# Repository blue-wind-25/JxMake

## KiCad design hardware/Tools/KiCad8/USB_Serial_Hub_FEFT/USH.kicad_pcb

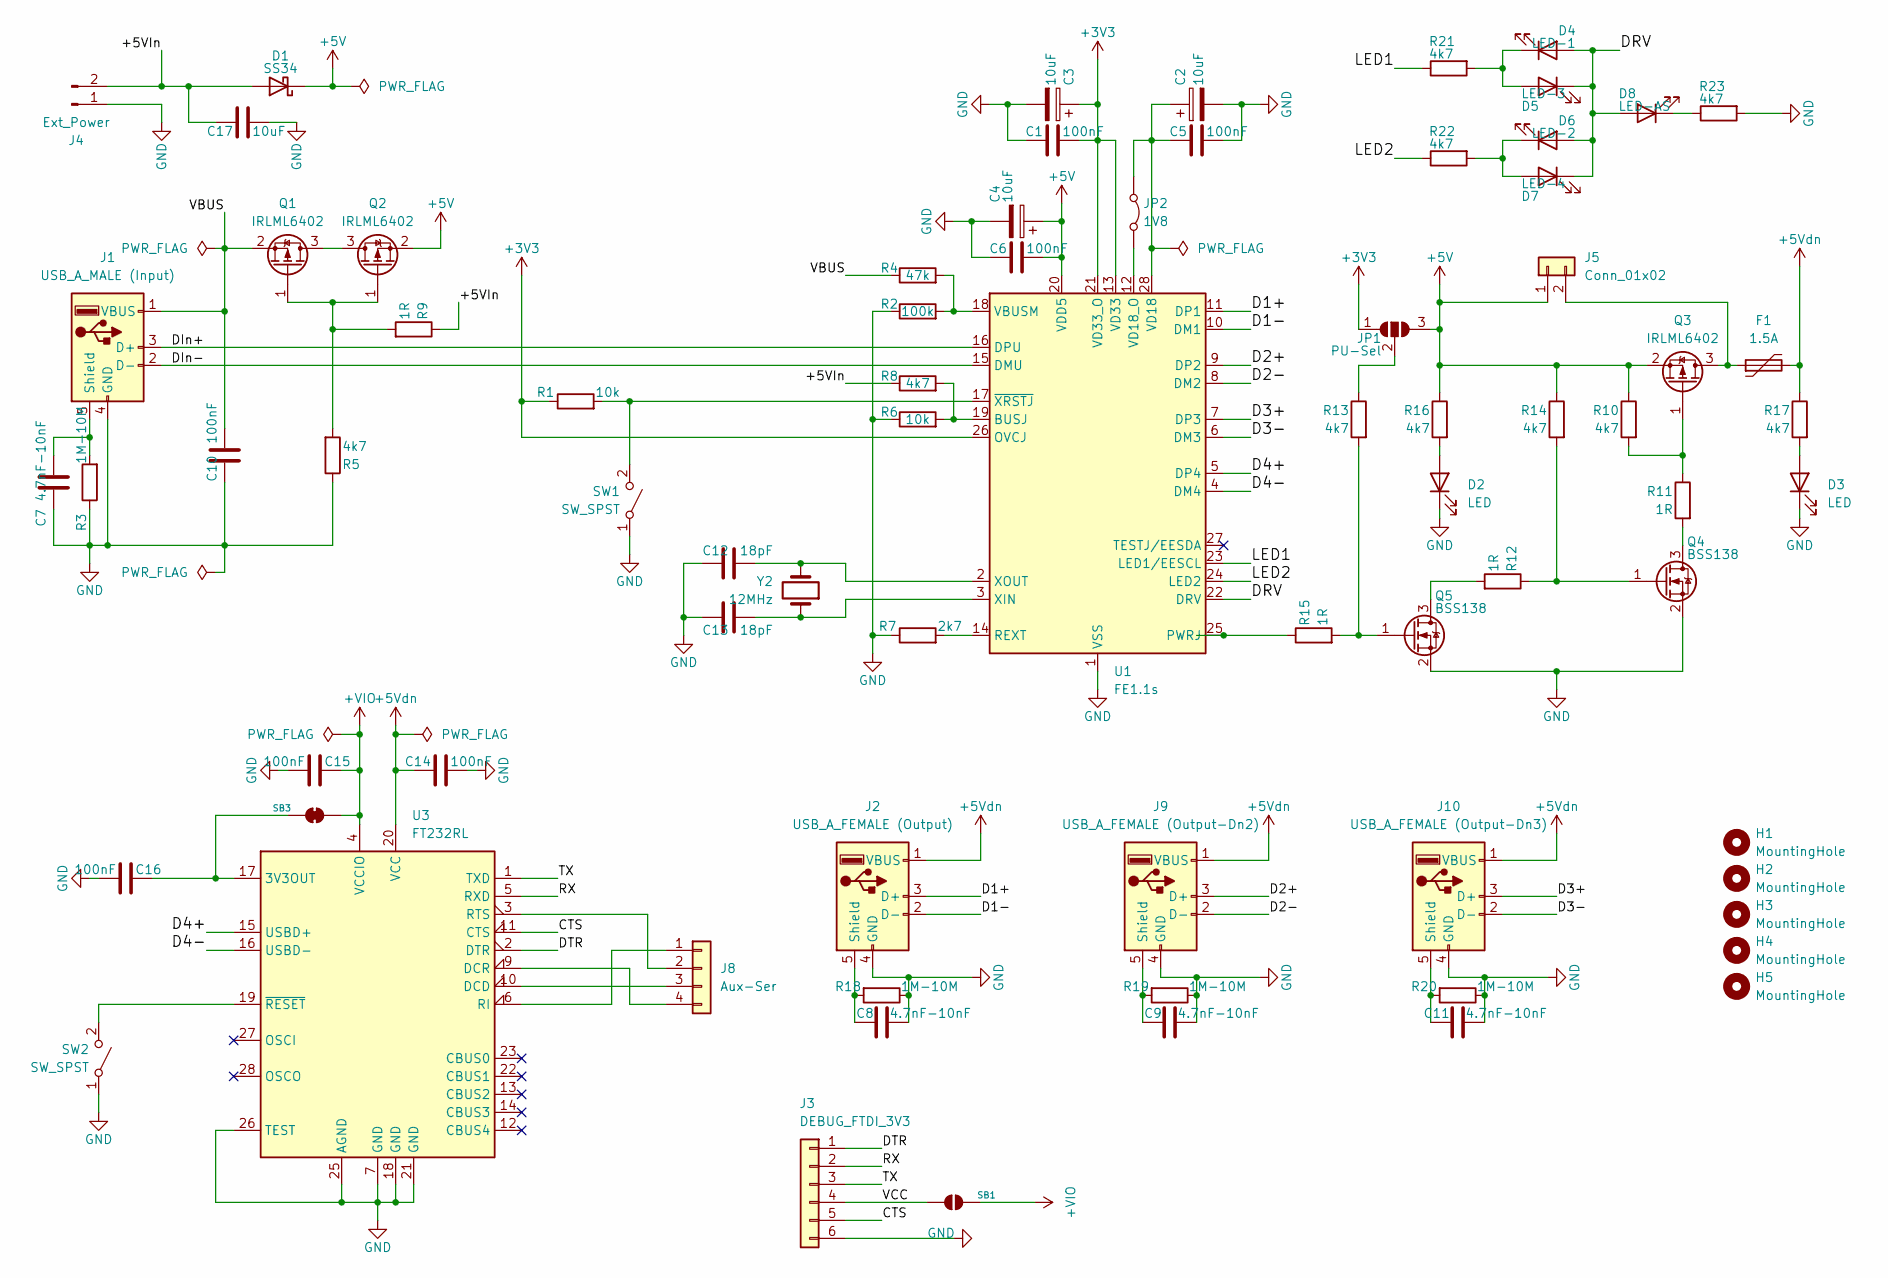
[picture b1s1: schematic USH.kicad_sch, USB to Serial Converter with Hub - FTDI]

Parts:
C1, C5, C6, C10, C14, C15, C16: 100nF; C_0805_2012Metric_Pad1.18x1.45mm_HandSolder
C2, C3, C4: 10uF; CP_EIA-3528-21_Kemet-B_Pad1.50x2.35mm_HandSolder
C7, C8, C9, C11: 4.7nF-10nF; C_0805_2012Metric_Pad1.18x1.45mm_HandSolder
C12, C13: 18pF; C_0805_2012Metric_Pad1.18x1.45mm_HandSolder
C17: 10uF; C_0805_2012Metric_Pad1.18x1.45mm_HandSolder
D1: SS34; D_SMB-SMC_Universal_Handsoldering
D2, D3: LED; LED_0805_2012Metric_Pad1.15x1.40mm_HandSolder
D4: LED-1; LED_0603_1608Metric_Pad1.05x0.95mm_HandSolder
D5: LED-3; LED_0603_1608Metric_Pad1.05x0.95mm_HandSolder
D6: LED-2; LED_0603_1608Metric_Pad1.05x0.95mm_HandSolder
D7: LED-4; LED_0603_1608Metric_Pad1.05x0.95mm_HandSolder
D8: LED-AS; LED_0603_1608Metric_Pad1.05x0.95mm_HandSolder
F1: 1.5A; R_1812_4532Metric_Pad1.30x3.40mm_HandSolder
H1, H2, H3, H4, H5: MountingHole; MountingHole_3.2mm_M3
J1: USB_A_MALE (Input); USB_A_CONNFLY_DS1095-WNR0
J2: USB_A_FEMALE (Output); USB_A_CONNFLY_DS1095-WNR0
J3: DEBUG_FTDI_3V3; PinHeader_1x06_P2.54mm_Horizontal
J4: Ext_Power; Molex_Nano-Fit_105313-xx02_1x02_P2.50mm_Horizontal
J5: Conn_01x02; PinHeader_1x02_P2.54mm_Vertical
J8: Aux-Ser; PinHeader_1x04_P1.00mm_Vertical
J9: USB_A_FEMALE (Output-Dn2); USB_A_CONNFLY_DS1095-WNR0
J10: USB_A_FEMALE (Output-Dn3); USB_A_CONNFLY_DS1095-WNR0
JP1: PU-Sel; SolderJumper-3_P1.3mm_Open_RoundedPad1.0x1.5mm
JP2: 1V8; SolderJumper-2_P1.3mm_Bridged_RoundedPad1.0x1.5mm
Q1, Q2, Q3: IRLML6402; SOT-23_Handsoldering
Q4, Q5: BSS138; SOT-23_Handsoldering
R1, R6: 10k; R_0805_2012Metric_Pad1.20x1.40mm_HandSolder
R2: 100k; R_0805_2012Metric_Pad1.20x1.40mm_HandSolder
R3, R18, R19, R20: 1M-10M; R_0805_2012Metric_Pad1.20x1.40mm_HandSolder
R4: 47k; R_0805_2012Metric_Pad1.20x1.40mm_HandSolder
R5, R8, R10, R13, R14, R16, R17: 4k7; R_0805_2012Metric_Pad1.20x1.40mm_HandSolder
R7: 2k7; R_0805_2012Metric_Pad1.20x1.40mm_HandSolder
R9, R11, R12, R15: 1R; R_0805_2012Metric_Pad1.20x1.40mm_HandSolder
R21, R22, R23: 4k7; R_0603_1608Metric_Pad0.98x0.95mm_HandSolder
SB1: Jumper_2_Small_Bridged; SolderJumper-2_P1.3mm_Open_RoundedPad1.0x1.5mm
SB3: Jumper_2_Small_Bridged; SolderJumper-2_P1.3mm_Bridged_RoundedPad1.0x1.5mm
SW1, SW2: SW_SPST; SW_SPST_FSMSM
U1: FE1.1s; SSOP-28_3.9x9.9mm_P0.635mm
U3: FT232RL; SSOP-28_5.3x10.2mm_P0.65mm
Y2: 12MHz; Crystal_SMD_HC49-SD

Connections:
+3V3: C1.1, C3.1, JP1.1 (A), R1.1, U1.13 (VD33), U1.21 (VD33_O), U1.26 (OVCJ)
+5V: C4.1, C6.1, D1.1 (K), J5.1, JP1.3 (B), Q2.2 (S), Q3.2 (S), R10.1, R14.1, R16.1, U1.20 (VDD5)
+5Vdn: C14.2, F1.2, J2.1 (VBUS), J9.1 (VBUS), J10.1 (VBUS), R17.1, U3.20 (VCC)
+VIO: C15.2, SB1.1 (A), SB3.2 (B), U3.4 (VCCIO)
/+5VIn: C17.2, D1.2 (A), J4.2, R8.1, R9.1
/CTS: J3.5, U3.11 (CTS)
/D1+: J2.3 (D+), U1.11 (DP1)
/D1-: J2.2 (D-), U1.10 (DM1)
/D2+: J9.3 (D+), U1.9 (DP2)
/D2-: J9.2 (D-), U1.8 (DM2)
/D3+: J10.3 (D+), U1.7 (DP3)
/D3-: J10.2 (D-), U1.6 (DM3)
/D4+: U1.5 (DP4), U3.15 (USBD+)
/D4-: U1.4 (DM4), U3.16 (USBD-)
/DIn+: J1.3 (D+), U1.16 (DPU)
/DIn-: J1.2 (D-), U1.15 (DMU)
/DRV: D4.2 (A), D5.1 (K), D6.2 (A), D7.1 (K), D8.2 (A), U1.22 (DRV)
/DTR: J3.1, U3.2 (DTR)
/LED1: R21.1, U1.23 (LED1/EESCL)
/LED2: R22.1, U1.24 (LED2)
/RX: J3.2, U3.5 (RXD)
/TX: J3.3, U3.1 (TXD)
/VBUS: C10.2, J1.1 (VBUS), Q1.2 (S), R4.1
/VCC: J3.4, SB1.2 (B)
GND: C1.2, C2.2, C3.2, C4.2, C5.1, C6.2, C7.1, C8.1, C9.1, C10.1, C11.1, C12.1, C13.1, C14.1, C15.1, C16.1, C17.1, D2.1 (K), D3.1 (K), J1.4 (GND), J2.4 (GND), J3.6, J4.1, J9.4 (GND), J10.4 (GND), Q4.2 (S), Q5.2 (S), R2.1, R3.1, R5.1, R6.1, R7.1, R18.1, R19.1, R20.1, R23.2, SW1.1 (A), SW2.1 (A), U1.1 (VSS), U3.7 (GND), U3.18 (GND), U3.21 (GND), U3.25 (AGND), U3.26 (TEST)
unnamed: D2.2 (A), R16.2
unnamed: D3.2 (A), R17.2
unnamed: D4.1 (K), D5.2 (A), R21.2
unnamed: D6.1 (K), D7.2 (A), R22.2
unnamed: D8.1 (K), R23.1
unnamed: C7.2, J1.5 (Shield), R3.2
unnamed: C8.2, J2.5 (Shield), R18.2
unnamed: F1.1, J5.2, Q3.3 (D)
unnamed: J8.1, U3.6 (RI)
unnamed: J8.2, U3.3 (RTS)
unnamed: J8.3, U3.10 (DCD)
unnamed: J8.4, U3.9 (DCR)
unnamed: C9.2, J9.5 (Shield), R19.2
unnamed: C11.2, J10.5 (Shield), R20.2
unnamed: JP1.2 (C), R13.1
unnamed: C2.1, C5.2, JP2.1 (A), U1.28 (VD18)
unnamed: JP2.2 (B), U1.12 (VD18_O)
unnamed: Q1.3 (D), Q2.3 (D)
unnamed: Q1.1 (G), Q2.1 (G), R5.2, R9.2
unnamed: Q3.1 (G), R10.2, R11.1
unnamed: Q4.3 (D), R11.2
unnamed: Q4.1 (G), R12.1, R14.2
unnamed: Q5.3 (D), R12.2
unnamed: Q5.1 (G), R13.2, R15.2
unnamed: C16.2, SB3.1 (A), U3.17 (3V3OUT)
unnamed: R1.2, SW1.2 (B), U1.17 (~XRSTJ)
unnamed: SW2.2 (B), U3.19 (~RESET)
unnamed: R6.2, R8.2, U1.19 (BUSJ)
unnamed: R15.1, U1.25 (PWRJ)
unnamed: R7.2, U1.14 (REXT)
unnamed: R2.2, R4.2, U1.18 (VBUSM)
unnamed: C13.2, U1.3 (XIN), Y2.1
unnamed: C12.2, U1.2 (XOUT), Y2.2

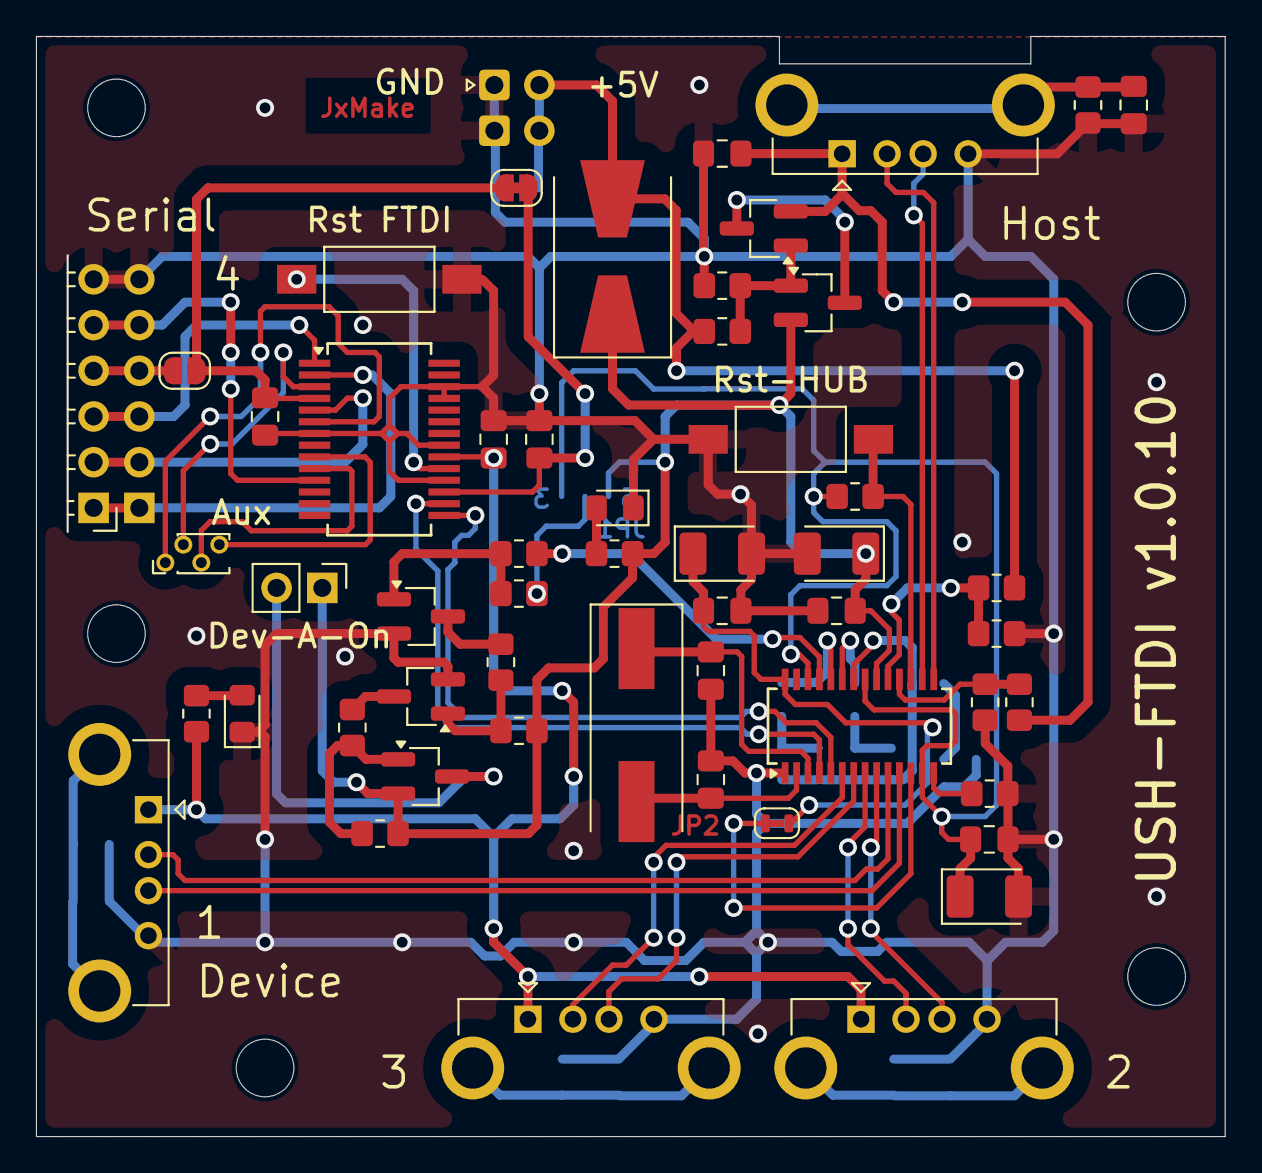
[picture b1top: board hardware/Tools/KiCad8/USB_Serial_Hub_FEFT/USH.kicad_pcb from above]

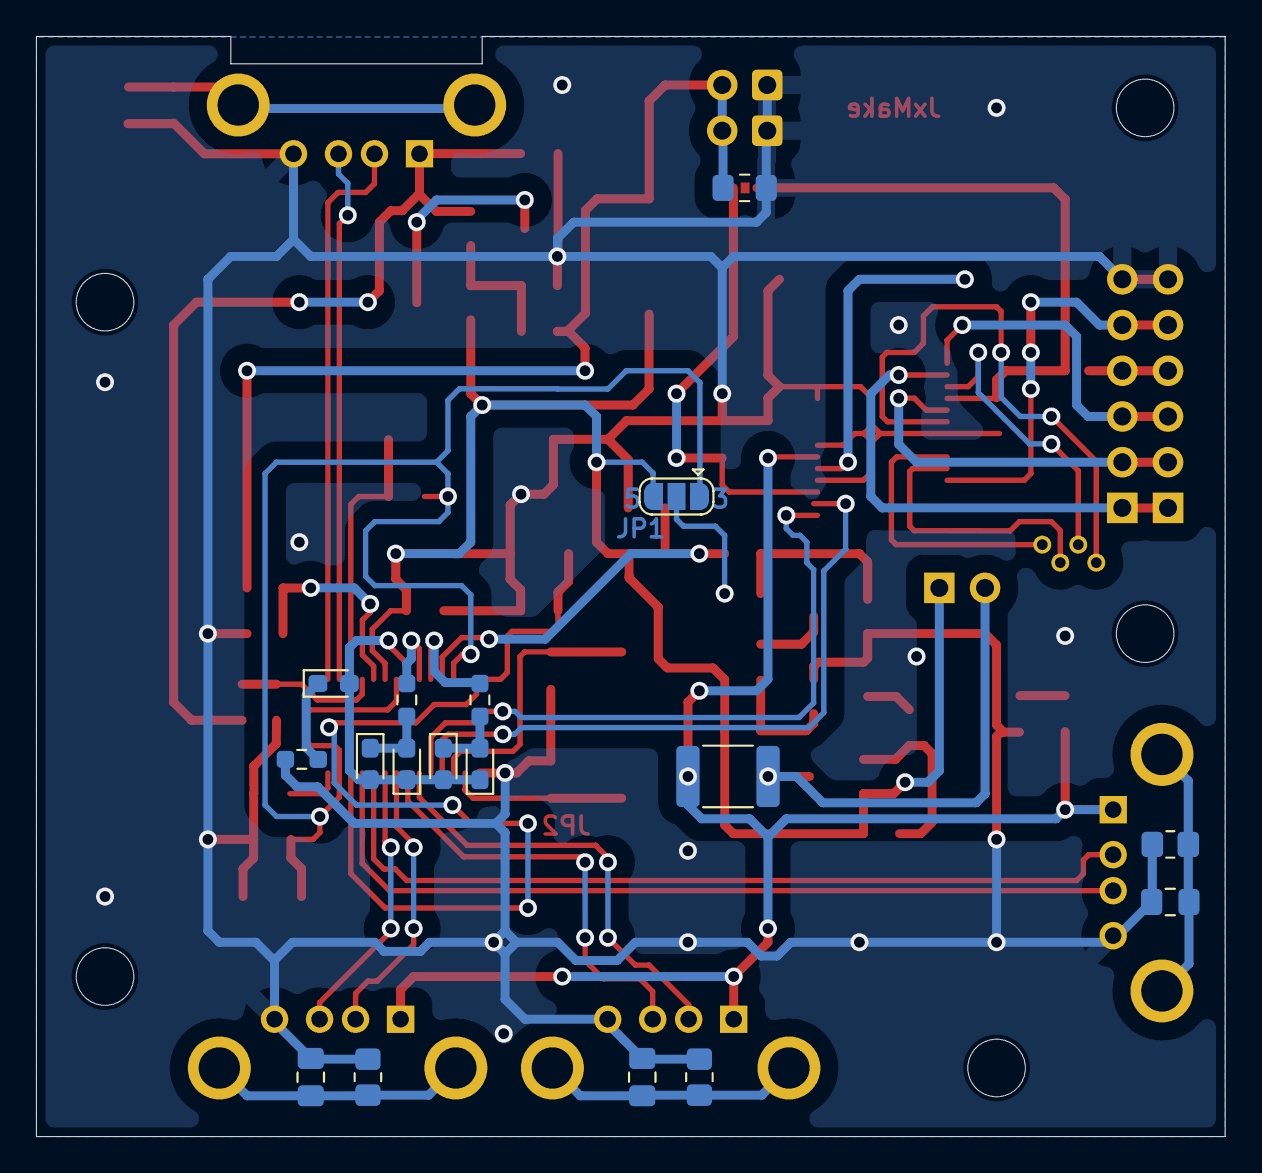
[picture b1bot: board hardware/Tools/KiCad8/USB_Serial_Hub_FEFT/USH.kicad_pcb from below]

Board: 2 copper layers, 66.0 x 61.1 mm, 76 parts (18 on the bottom side), 58 nets.

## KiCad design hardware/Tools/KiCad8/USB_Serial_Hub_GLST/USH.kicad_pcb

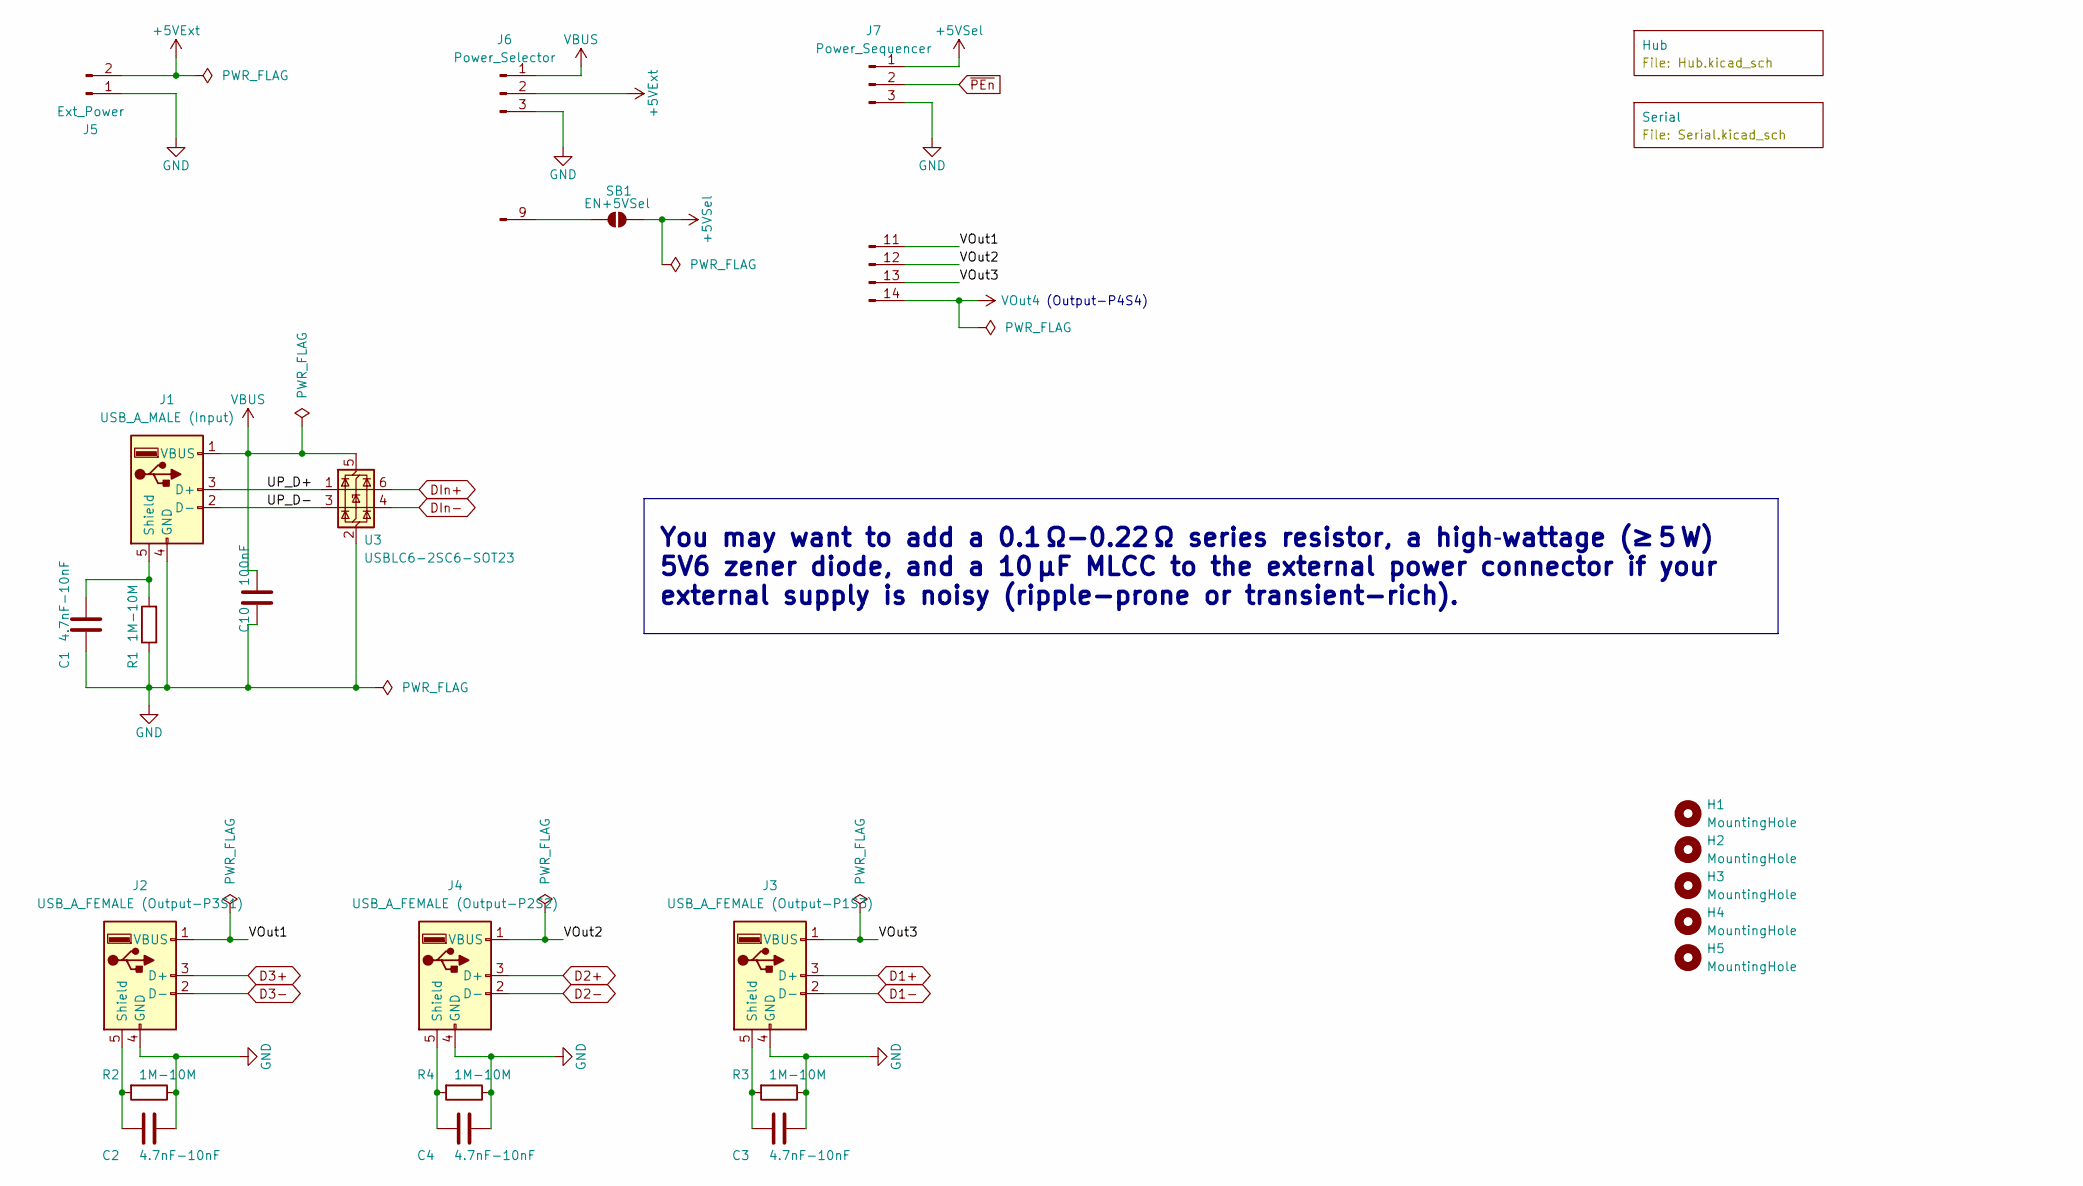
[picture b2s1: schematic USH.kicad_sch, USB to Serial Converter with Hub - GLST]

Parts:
C1, C2, C3, C4: 4.7nF-10nF; C_0805_2012Metric_Pad1.18x1.45mm_HandSolder
C10: 100nF; C_0805_2012Metric_Pad1.18x1.45mm_HandSolder
H1, H2, H3, H4, H5: MountingHole; MountingHole_3.2mm_M3
J1: USB_A_MALE (Input); USB_A_CONNFLY_DS1095-WNR0
J2: USB_A_FEMALE (Output-P3S1); USB_A_CONNFLY_DS1095-WNR0
J3: USB_A_FEMALE (Output-P1S3); USB_A_CONNFLY_DS1095-WNR0
J4: USB_A_FEMALE (Output-P2S2); USB_A_CONNFLY_DS1095-WNR0
J5: Ext_Power; Molex_Nano-Fit_105313-xx02_1x02_P2.50mm_Horizontal
J6: Power_Selector; PinHeader_1x09_P2.54mm_Vertical
J7: Power_Sequencer; PinHeader_1x14_P2.54mm_Vertical
R1, R2, R3, R4: 1M-10M; R_0805_2012Metric_Pad1.20x1.40mm_HandSolder
SB1: EN+5VSel; SolderJumper-2_P1.3mm_Open_RoundedPad1.0x1.5mm
U3: USBLC6-2SC6-SOT23; SOT-23-6

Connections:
+5VExt: J5.2, J6.2; also elsewhere on the board
+5VSel: J7.1, SB1.1 (A); also elsewhere on the board
/UP_D+: J1.3 (D+), U3.1 (I/O1)
/UP_D-: J1.2 (D-), U3.3 (I/O2)
/VOut1: J2.1 (VBUS), J7.11
/VOut2: J4.1 (VBUS), J7.12
/VOut3: J3.1 (VBUS), J7.13
D1+: J3.3 (D+); also elsewhere on the board
D1-: J3.2 (D-); also elsewhere on the board
D2+: J4.3 (D+); also elsewhere on the board
D2-: J4.2 (D-); also elsewhere on the board
D3+: J2.3 (D+); also elsewhere on the board
D3-: J2.2 (D-); also elsewhere on the board
DIn+: U3.6 (I/O1); also elsewhere on the board
DIn-: U3.4 (I/O2); also elsewhere on the board
GND: C1.1, C2.1, C3.1, C4.1, C10.1, J1.4 (GND), J2.4 (GND), J3.4 (GND), J4.4 (GND), J5.1, J6.3, J7.3, R1.1, R2.1, R3.1, R4.1, U3.2 (GND); also elsewhere on the board
unnamed: C1.2, J1.5 (Shield), R1.2
unnamed: C2.2, J2.5 (Shield), R2.2
unnamed: C3.2, J3.5 (Shield), R3.2
unnamed: C4.2, J4.5 (Shield), R4.2
unnamed: J6.9, SB1.2 (B)
VBUS: C10.2, J1.1 (VBUS), J6.1, U3.5 (VBUS); also elsewhere on the board
VOut4: J7.14; also elsewhere on the board
~PEn: J7.2; also elsewhere on the board

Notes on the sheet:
You may want to add a 0.1 Ω-0.22 Ω series resistor, a high‑wattage (≥ 5 W) 5V6 zener diode, and a 10 µF MLCC to the external power connector if your external supply is noisy (ripple-prone or transient-rich).
(Output-P4S4)

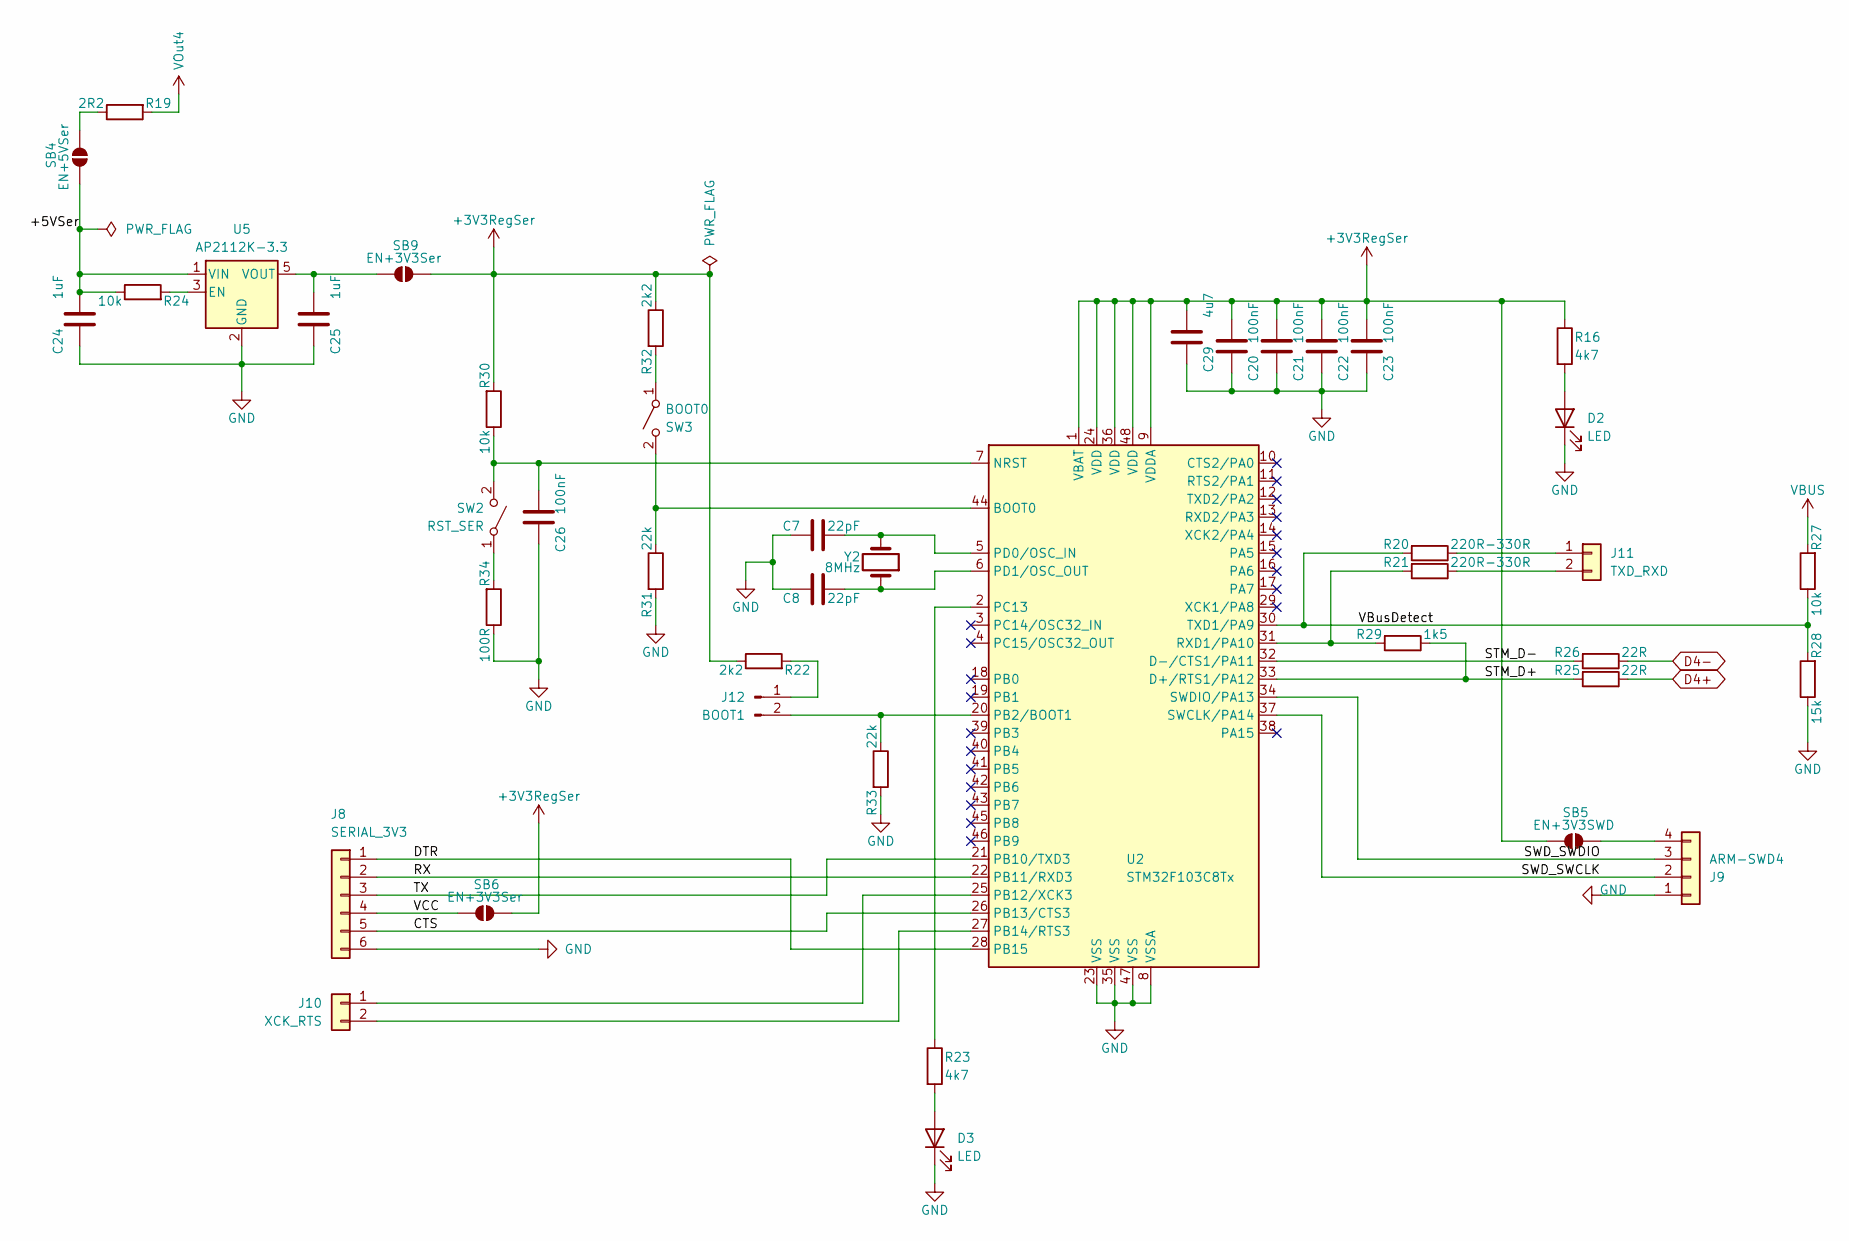
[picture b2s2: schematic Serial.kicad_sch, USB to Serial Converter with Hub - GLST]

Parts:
C7, C8: 22pF; C_0805_2012Metric_Pad1.18x1.45mm_HandSolder
C20, C21, C22, C23, C26: 100nF; C_0805_2012Metric_Pad1.18x1.45mm_HandSolder
C24, C25: 1uF; C_0805_2012Metric_Pad1.18x1.45mm_HandSolder
C29: 4u7; C_0805_2012Metric_Pad1.18x1.45mm_HandSolder
D2, D3: LED; LED_0805_2012Metric_Pad1.15x1.40mm_HandSolder
J8: SERIAL_3V3; PinHeader_1x06_P2.54mm_Horizontal
J9: ARM-SWD4; PinHeader_1x04_P2.54mm_Horizontal
J10: XCK_RTS; PinHeader_1x02_P2.54mm_Vertical
J11: TXD_RXD; PinHeader_1x02_P2.54mm_Vertical
J12: BOOT1; PinHeader_1x02_P2.54mm_Vertical
R16, R23: 4k7; R_0805_2012Metric_Pad1.20x1.40mm_HandSolder
R19: 2R2; R_0805_2012Metric_Pad1.20x1.40mm_HandSolder
R20, R21: 220R-330R; R_0805_2012Metric_Pad1.20x1.40mm_HandSolder
R22, R32: 2k2; R_0805_2012Metric_Pad1.20x1.40mm_HandSolder
R24, R27, R30: 10k; R_0805_2012Metric_Pad1.20x1.40mm_HandSolder
R25, R26: 22R; R_0805_2012Metric_Pad1.20x1.40mm_HandSolder
R28: 15k; R_0805_2012Metric_Pad1.20x1.40mm_HandSolder
R29: 1k5; R_0805_2012Metric_Pad1.20x1.40mm_HandSolder
R31, R33: 22k; R_0805_2012Metric_Pad1.20x1.40mm_HandSolder
R34: 100R; R_0805_2012Metric_Pad1.20x1.40mm_HandSolder
SB4: EN+5VSer; SolderJumper-2_P1.3mm_Open_RoundedPad1.0x1.5mm
SB5: EN+3V3SWD; SolderJumper-2_P1.3mm_Open_RoundedPad1.0x1.5mm
SB6, SB9: EN+3V3Ser; SolderJumper-2_P1.3mm_Open_RoundedPad1.0x1.5mm
SW2: RST_SER; SW_SPST_CK_RS282G05A3
SW3: BOOT0; SW_SPST_CK_RS282G05A3
U2: STM32F103C8Tx; gl852_lqfp48
U5: AP2112K-3.3; SOT-23-5
Y2: 8MHz; Crystal_SMD_HC49-SD

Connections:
+3V3RegSer: C20.2, C21.2, C22.2, C23.2, C29.2, R16.1, R22.1, R30.2, R32.1, SB5.2 (B), SB6.1 (A), SB9.1 (A), U2.1 (VBAT), U2.9 (VDDA), U2.24 (VDD), U2.36 (VDD), U2.48 (VDD)
/Serial/+5VSer: C24.2, R24.1, SB4.2 (B), U5.1 (VIN)
/Serial/CTS: J8.5, U2.26 (PB13/CTS3)
/Serial/DTR: J8.1, U2.28 (PB15)
/Serial/RX: J8.2, U2.22 (PB11/RXD3)
/Serial/STM_D+: R25.2, R29.1, U2.33 (D+/RTS1/PA12)
/Serial/STM_D-: R26.2, U2.32 (D-/CTS1/PA11)
/Serial/SWD_SWCLK: J9.2, U2.37 (SWCLK/PA14)
/Serial/SWD_SWDIO: J9.3, U2.34 (SWDIO/PA13)
/Serial/TX: J8.3, U2.21 (PB10/TXD3)
/Serial/VBusDetect: R20.2, R27.1, R28.2, U2.30 (TXD1/PA9)
/Serial/VCC: J8.4, SB6.2 (B)
D4+: R25.1; also elsewhere on the board
D4-: R26.1; also elsewhere on the board
GND: C7.1, C8.1, C20.1, C21.1, C22.1, C23.1, C24.1, C25.1, C26.1, C29.1, D2.1 (K), D3.1 (K), J8.6, J9.1, R28.1, R31.2, R33.2, R34.1, U2.8 (VSSA), U2.23 (VSS), U2.35 (VSS), U2.47 (VSS), U5.2 (GND); also elsewhere on the board
unnamed: D2.2 (A), R16.2
unnamed: D3.2 (A), R23.2
unnamed: J9.4, SB5.1 (A)
unnamed: J10.1, U2.25 (PB12/XCK3)
unnamed: J10.2, U2.27 (PB14/RTS3)
unnamed: J11.1, R20.1
unnamed: J11.2, R21.1
unnamed: J12.1, R22.2
unnamed: J12.2, R33.1, U2.20 (PB2/BOOT1)
unnamed: R19.1, SB4.1 (A)
unnamed: C25.2, SB9.2 (B), U5.5 (VOUT)
unnamed: R34.2, SW2.1 (A)
unnamed: C26.2, R30.1, SW2.2 (B), U2.7 (NRST)
unnamed: R32.2, SW3.1 (A)
unnamed: R31.1, SW3.2 (B), U2.44 (BOOT0)
unnamed: R23.1, U2.2 (PC13)
unnamed: C7.2, U2.5 (PD0/OSC_IN), Y2.2
unnamed: C8.2, U2.6 (PD1/OSC_OUT), Y2.1
unnamed: R21.2, R29.2, U2.31 (RXD1/PA10)
unnamed: R24.2, U5.3 (EN)
VBUS: R27.2; also elsewhere on the board
VOut4: R19.2; also elsewhere on the board

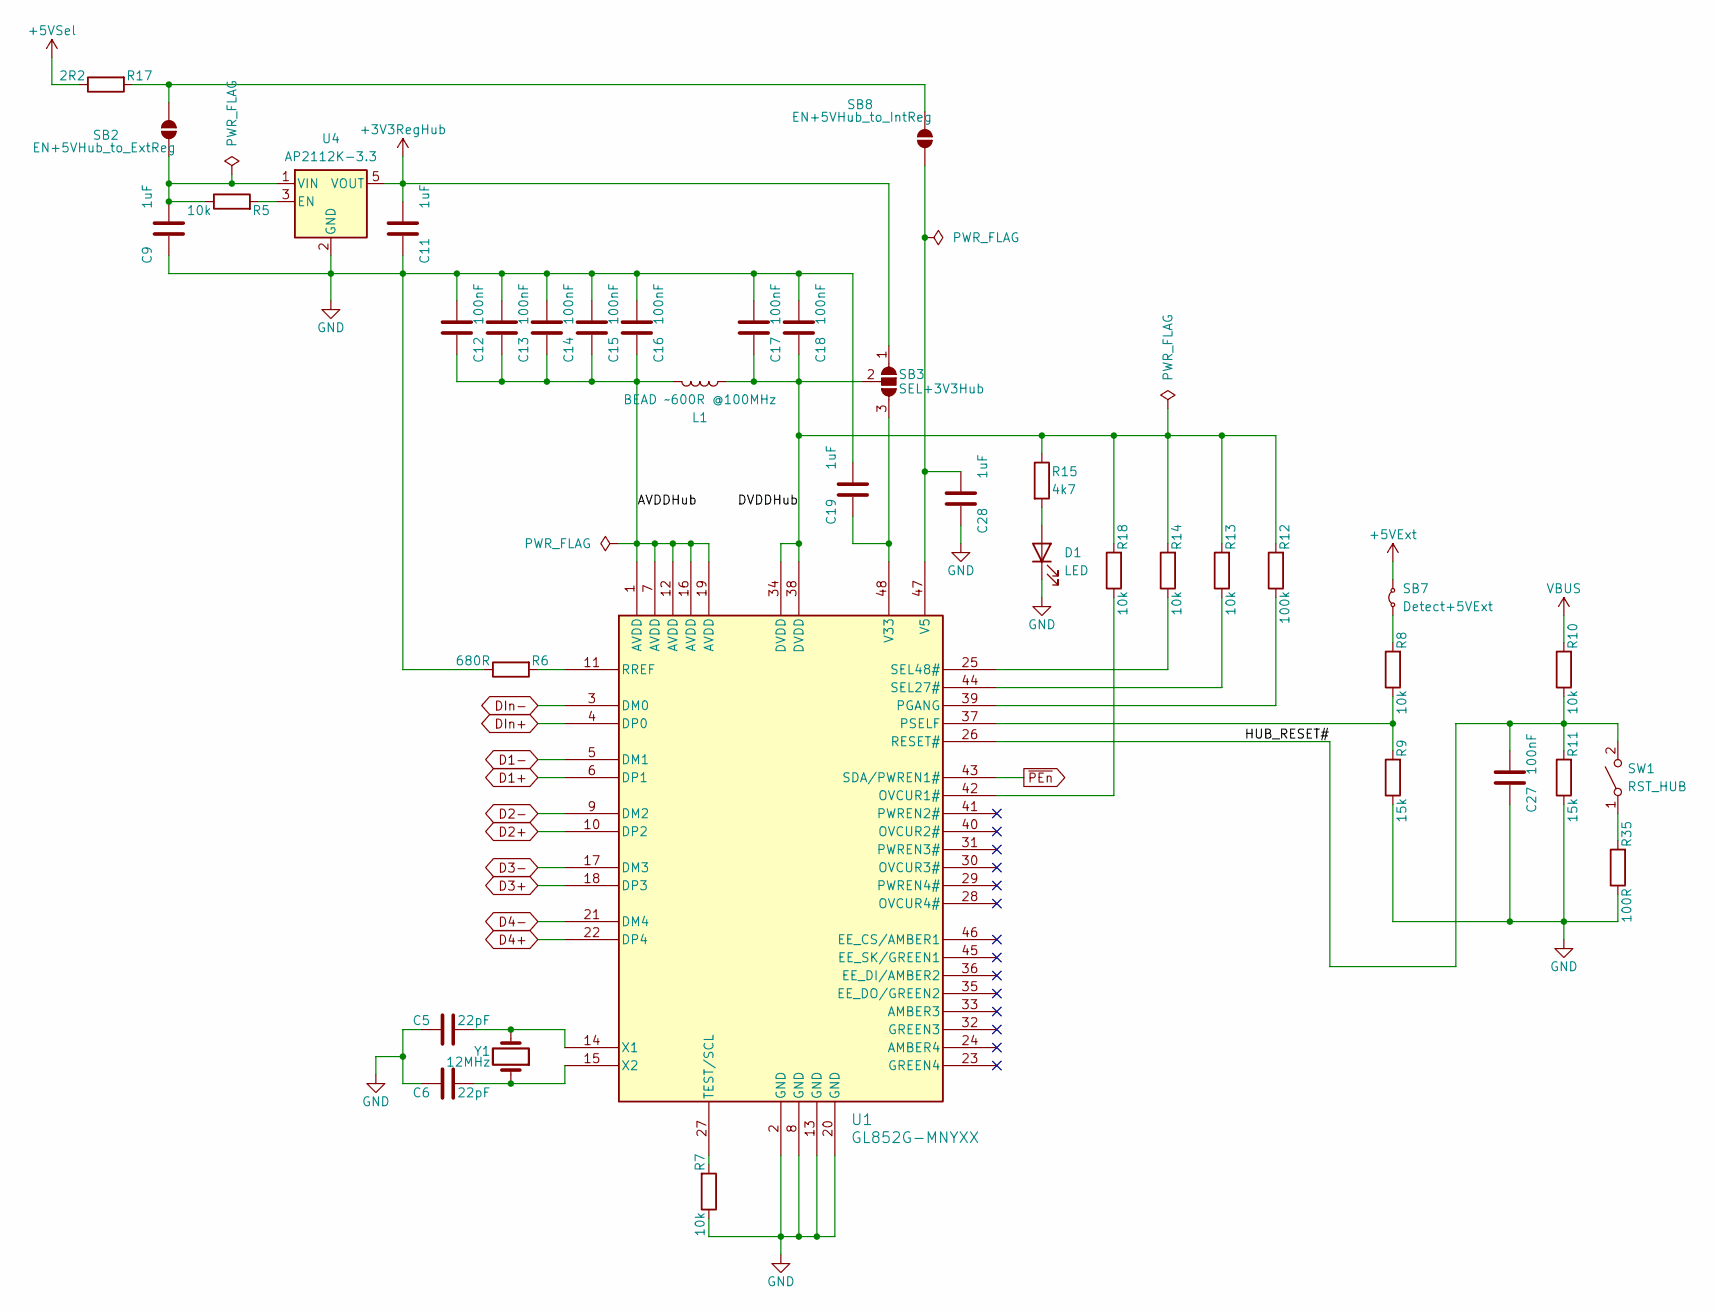
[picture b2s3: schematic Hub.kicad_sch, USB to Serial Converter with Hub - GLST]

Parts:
C5, C6: 22pF; C_0805_2012Metric_Pad1.18x1.45mm_HandSolder
C9, C11, C19, C28: 1uF; C_0805_2012Metric_Pad1.18x1.45mm_HandSolder
C12, C13, C14, C15, C16, C17, C18, C27: 100nF; C_0805_2012Metric_Pad1.18x1.45mm_HandSolder
D1: LED; LED_0805_2012Metric_Pad1.15x1.40mm_HandSolder
L1: BEAD ~600R @100MHz; L_0805_2012Metric_Pad1.15x1.40mm_HandSolder
R5, R7, R8, R10, R13, R14, R18: 10k; R_0805_2012Metric_Pad1.20x1.40mm_HandSolder
R6: 680R; R_0805_2012Metric_Pad1.20x1.40mm_HandSolder
R9, R11: 15k; R_0805_2012Metric_Pad1.20x1.40mm_HandSolder
R12: 100k; R_0805_2012Metric_Pad1.20x1.40mm_HandSolder
R15: 4k7; R_0805_2012Metric_Pad1.20x1.40mm_HandSolder
R17: 2R2; R_0805_2012Metric_Pad1.20x1.40mm_HandSolder
R35: 100R; R_0805_2012Metric_Pad1.20x1.40mm_HandSolder
SB2: EN+5VHub_to_ExtReg; SolderJumper-2_P1.3mm_Open_RoundedPad1.0x1.5mm
SB3: SEL+3V3Hub; SolderJumper-3_P1.3mm_Open_RoundedPad1.0x1.5mm
SB7: Detect+5VExt; SolderJumper-2_P1.3mm_Bridged_RoundedPad1.0x1.5mm
SB8: EN+5VHub_to_IntReg; SolderJumper-2_P1.3mm_Open_RoundedPad1.0x1.5mm
SW1: RST_HUB; SW_SPST_CK_RS282G05A3
U1: GL852G-MNYXX; gl852_lqfp48
U4: AP2112K-3.3; SOT-23-5
Y1: 12MHz; Crystal_SMD_HC49-SD

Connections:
+3V3RegHub: C11.2, SB3.1 (A), U4.5 (VOUT)
+5VExt: SB7.2 (B); also elsewhere on the board
+5VSel: R17.1; also elsewhere on the board
/Hub/AVDDHub: C12.1, C13.1, C14.1, C15.1, C16.1, L1.1, U1.1 (AVDD), U1.7 (AVDD), U1.12 (AVDD), U1.16 (AVDD), U1.19 (AVDD)
/Hub/DVDDHub: C17.1, C18.1, L1.2, R12.2, R13.2, R14.2, R15.1, R18.2, SB3.2 (C), U1.34 (DVDD), U1.38 (DVDD)
/Hub/HUB_RESET#: C27.2, R10.1, R11.2, SW1.2 (B), U1.26 (RESET#)
D1+: U1.6 (DP1); also elsewhere on the board
D1-: U1.5 (DM1); also elsewhere on the board
D2+: U1.10 (DP2); also elsewhere on the board
D2-: U1.9 (DM2); also elsewhere on the board
D3+: U1.18 (DP3); also elsewhere on the board
D3-: U1.17 (DM3); also elsewhere on the board
D4+: U1.22 (DP4); also elsewhere on the board
D4-: U1.21 (DM4); also elsewhere on the board
DIn+: U1.4 (DP0); also elsewhere on the board
DIn-: U1.3 (DM0); also elsewhere on the board
GND: C5.1, C6.1, C9.1, C11.1, C12.2, C13.2, C14.2, C15.2, C16.2, C17.2, C18.2, C19.2, C27.1, C28.1, D1.1 (K), R6.1, R7.1, R9.1, R11.1, R35.1, U1.2 (GND), U1.8 (GND), U1.13 (GND), U1.20 (GND), U4.2 (GND); also elsewhere on the board
unnamed: D1.2 (A), R15.2
unnamed: R17.2, SB2.1 (A), SB8.1 (A)
unnamed: C9.2, R5.1, SB2.2 (B), U4.1 (VIN)
unnamed: C19.1, SB3.3 (B), U1.48 (V33)
unnamed: R8.2, SB7.1 (A)
unnamed: C28.2, SB8.2 (B), U1.47 (V5)
unnamed: R35.2, SW1.1 (A)
unnamed: R18.1, U1.42 (OVCUR1#)
unnamed: R12.1, U1.39 (PGANG)
unnamed: R8.1, R9.2, U1.37 (PSELF)
unnamed: R6.2, U1.11 (RREF)
unnamed: R13.1, U1.44 (SEL27#)
unnamed: R14.1, U1.25 (SEL48#)
unnamed: R7.2, U1.27 (TEST/SCL)
unnamed: C5.2, U1.14 (X1), Y1.2
unnamed: C6.2, U1.15 (X2), Y1.1
unnamed: R5.2, U4.3 (EN)
VBUS: R10.2; also elsewhere on the board
~PEn: U1.43 (SDA/PWREN1#); also elsewhere on the board

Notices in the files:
hardware/Tools/KiCad8/USB_Serial_Hub_FEFT/USH.kicad_pcb:
This file is part of the JxMake program, see LICENSE file for the license details
Copyright (C) Aloysius Indrayanto
